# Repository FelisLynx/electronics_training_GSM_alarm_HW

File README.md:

# electronics_training_GSM_alarm_HW
Hardware for GSM alarm (electronics training group materials)

please check wiki for more information:
https://github.com/FelisLynx/electronics_training_GSM_alarm_HW/wiki

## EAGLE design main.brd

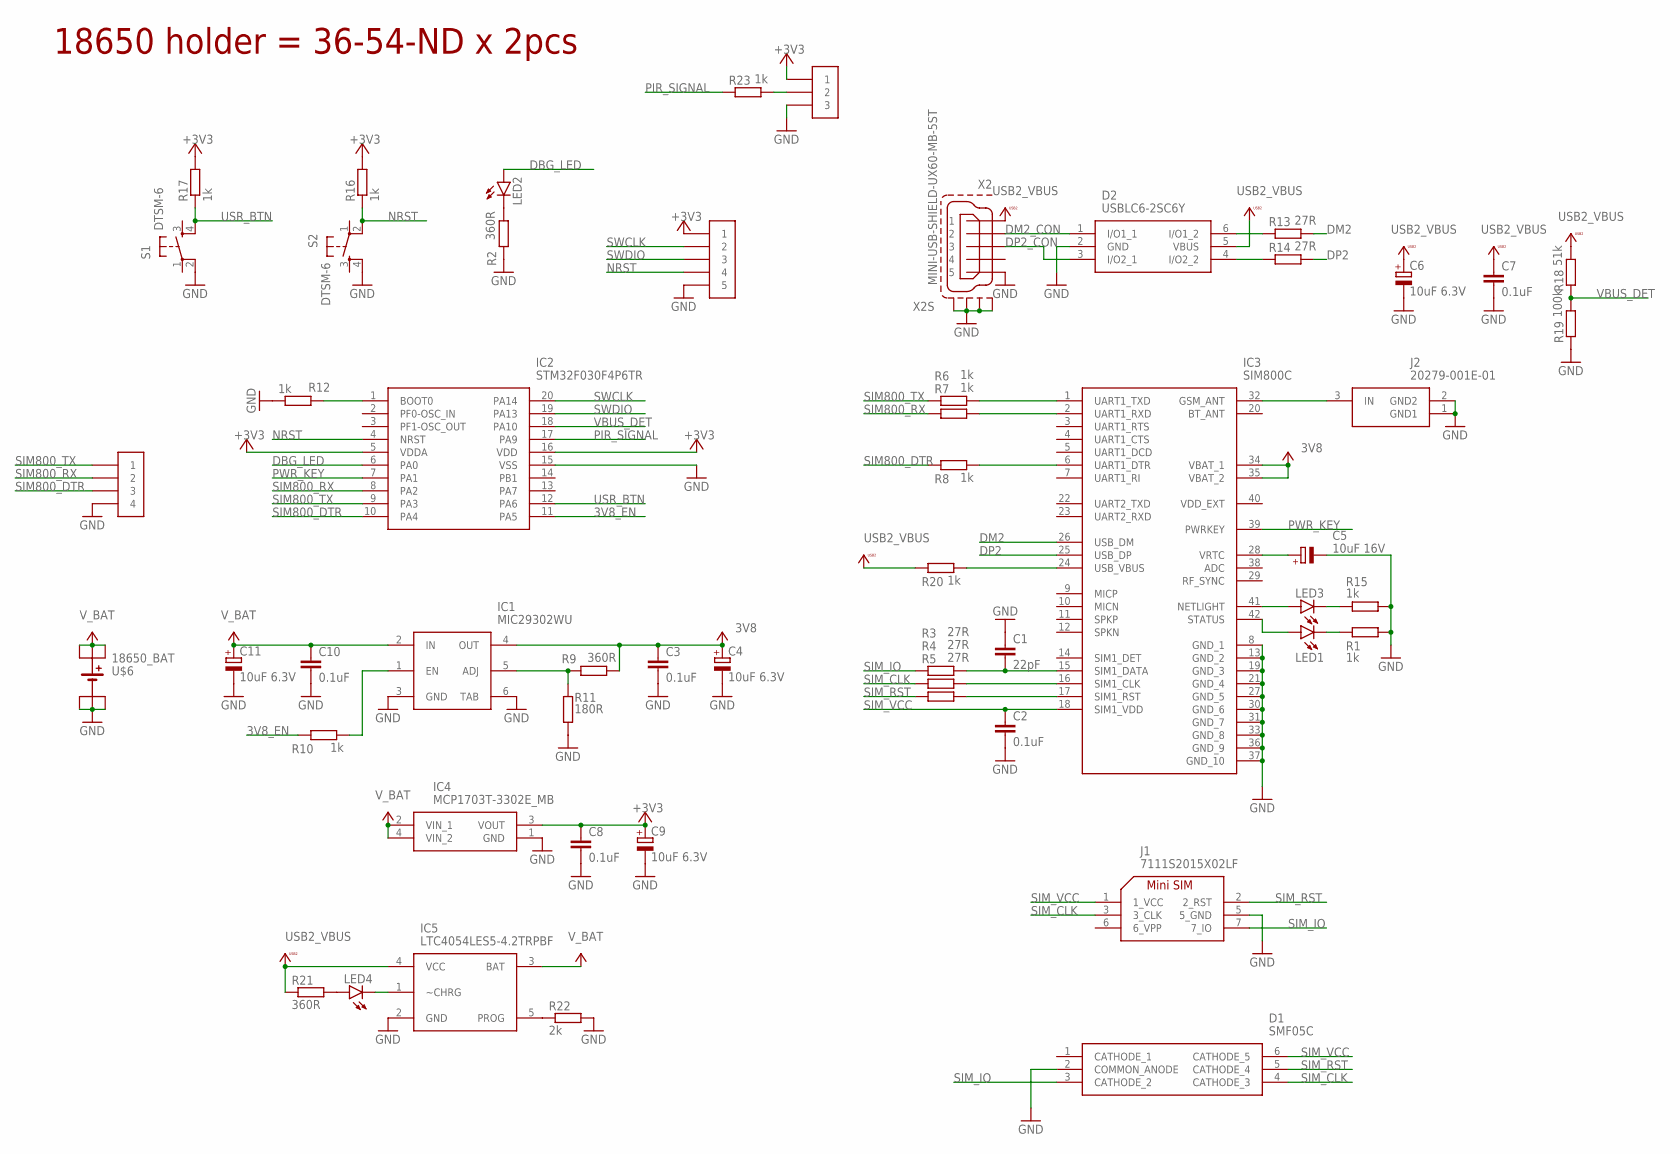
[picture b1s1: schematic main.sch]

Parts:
C1: 22pF; C0805
C2, C3, C7, C8, C10: 0.1uF; C0805
C4, C6, C9, C11: 10uF 6.3V; SMC_C
C5: 10uF 16V; SMC_C
D1: SMF05C; SOT65P210X110-6N
D2: USBLC6-2SC6Y; SOT95P280X145-6N
IC1: MIC29302WU
IC2: STM32F030F4P6TR; SOP65P640X120-20N
IC3: SIM800C
IC4: MCP1703T-3302E_MB; SOT-89(MB)
IC5: LTC4054LES5-4.2TRPBF; SOT95P280X100-5N
J1: 7111S2015X02LF
J2: 20279-001E-01
LED1, LED2, LED3, LED4: LEDCHIPLED_0805; CHIPLED_0805
R1, R6, R7, R8, R10, R12, R15, R16, R17, R20, R23: 1k; R0805
R2, R9, R21: 360R; R0805
R3, R4, R5, R13, R14: 27R; R0805
R11: 180R; R0805
R18: 51k; R0805
R19: 100k; R0805
R22: 2k; R0805
S1, S2: DTSM-6
U$5: 1R_4P
U$6: 18650_BAT
U$12: 1R_5P
U$15: 1R_3P
X2: MINI-USB-SHIELD-UX60-MB-5ST; UX60-MB-5ST

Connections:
3V8: C3.1, C4.+, IC1.4 (OUT), IC3.34 (VBAT_1), IC3.35 (VBAT_2), R9.2
3V8_EN: IC2.11 (PA5), R10.1
+3V3: C8.1, C9.+, IC2.5 (VDDA), IC2.16 (VDD), IC4.3 (VOUT), R16.2, R17.2, U$12.P$1 (1), U$15.P$1 (1)
DBG_LED: IC2.6 (PA0), LED2.A
DM2: IC3.26 (USB_DM), R13.2
DM2_CON: D2.1 (I/O1_1), X2.2
DP2: IC3.25 (USB_DP), R14.2
DP2_CON: D2.3 (I/O2_1), X2.3
GND: C1.1, C2.2, C3.2, C4.-, C5.-, C6.-, C7.2, C8.2, C9.-, C10.2, C11.-, D1.2 (COMMON_ANODE), D2.2 (GND), IC1.3 (GND), IC1.6 (TAB), IC2.15 (VSS), IC3.8 (GND_1), IC3.13 (GND_2), IC3.19 (GND_3), IC3.21 (GND_4), IC3.27 (GND_5), IC3.30 (GND_6), IC3.31 (GND_7), IC3.33 (GND_8), IC3.36 (GND_9), IC3.37 (GND_10), IC4.1 (GND), IC5.2 (GND), J1.5 (5_GND), J2.1 (GND1), J2.2 (GND2), R1.2, R2.1, R11.1, R12.2, R15.2, R19.1, R22.2, S1.2, S2.4, U$5.P$4 (4), U$6.4, U$6.5, U$6.6, U$12.P$5 (5), U$15.P$3 (3), X2.5, X2.M1 (S1), X2.M2 (S2), X2.M3 (S3), X2.M4 (S4)
unnamed: IC3.41 (NETLIGHT), LED3.A
unnamed: LED3.C, R15.1
unnamed: IC3.42 (STATUS), LED1.A
unnamed: LED1.C, R1.1
unnamed: IC3.32 (GSM_ANT), J2.3 (IN)
unnamed: C5.+, IC3.28 (VRTC)
unnamed: C1.2, IC3.15 (SIM1_DATA), R3.2
unnamed: IC3.16 (SIM1_CLK), R4.2
unnamed: IC3.17 (SIM1_RST), R5.2
unnamed: IC2.1 (BOOT0), R12.1
unnamed: IC3.1 (UART1_TXD), R6.2
unnamed: IC3.2 (UART1_RXD), R7.2
unnamed: IC3.6 (UART1_DTR), R8.2
unnamed: IC1.1 (EN), R10.2
unnamed: D2.6 (I/O1_2), R13.1
unnamed: IC1.5 (ADJ), R9.1, R11.2
unnamed: LED2.C, R2.2
unnamed: IC3.24 (USB_VBUS), R20.2
unnamed: D2.4 (I/O2_2), R14.1
unnamed: LED4.A, R21.2
unnamed: IC5.1 (~CHRG), LED4.C
unnamed: IC5.5 (PROG), R22.1
unnamed: R23.2, U$15.P$2 (2)
NRST: IC2.4 (NRST), R16.1, S2.2, U$12.P$4 (4)
PIR_SIGNAL: IC2.17 (PA9), R23.1
PWR_KEY: IC2.7 (PA1), IC3.39 (PWRKEY)
SIM800_DTR: IC2.10 (PA4), R8.1, U$5.P$3 (3)
SIM800_RX: IC2.8 (PA2), R7.1, U$5.P$2 (2)
SIM800_TX: IC2.9 (PA3), R6.1, U$5.P$1 (1)
SIM_CLK: D1.4 (CATHODE_3), J1.3 (3_CLK), R4.1
SIM_IO: D1.3 (CATHODE_2), J1.7 (7_IO), R3.1
SIM_RST: D1.5 (CATHODE_4), J1.2 (2_RST), R5.1
SIM_VCC: C2.1, D1.6 (CATHODE_5), IC3.18 (SIM1_VDD), J1.1 (1_VCC)
SWCLK: IC2.20 (PA14), U$12.P$2 (2)
SWDIO: IC2.19 (PA13), U$12.P$3 (3)
USB2_VBUS: C6.+, C7.1, D2.5 (VBUS), IC5.4 (VCC), R18.2, R20.1, R21.1, X2.1
USR_BTN: IC2.12 (PA6), R17.1, S1.4
VBUS_DET: IC2.18 (PA10), R18.1, R19.2
V_BAT: C10.1, C11.+, IC1.2 (IN), IC4.2 (VIN_1), IC4.4 (VIN_2), IC5.3 (BAT), U$6.1, U$6.2, U$6.3

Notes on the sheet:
18650 holder = 36-54-ND x 2pcs

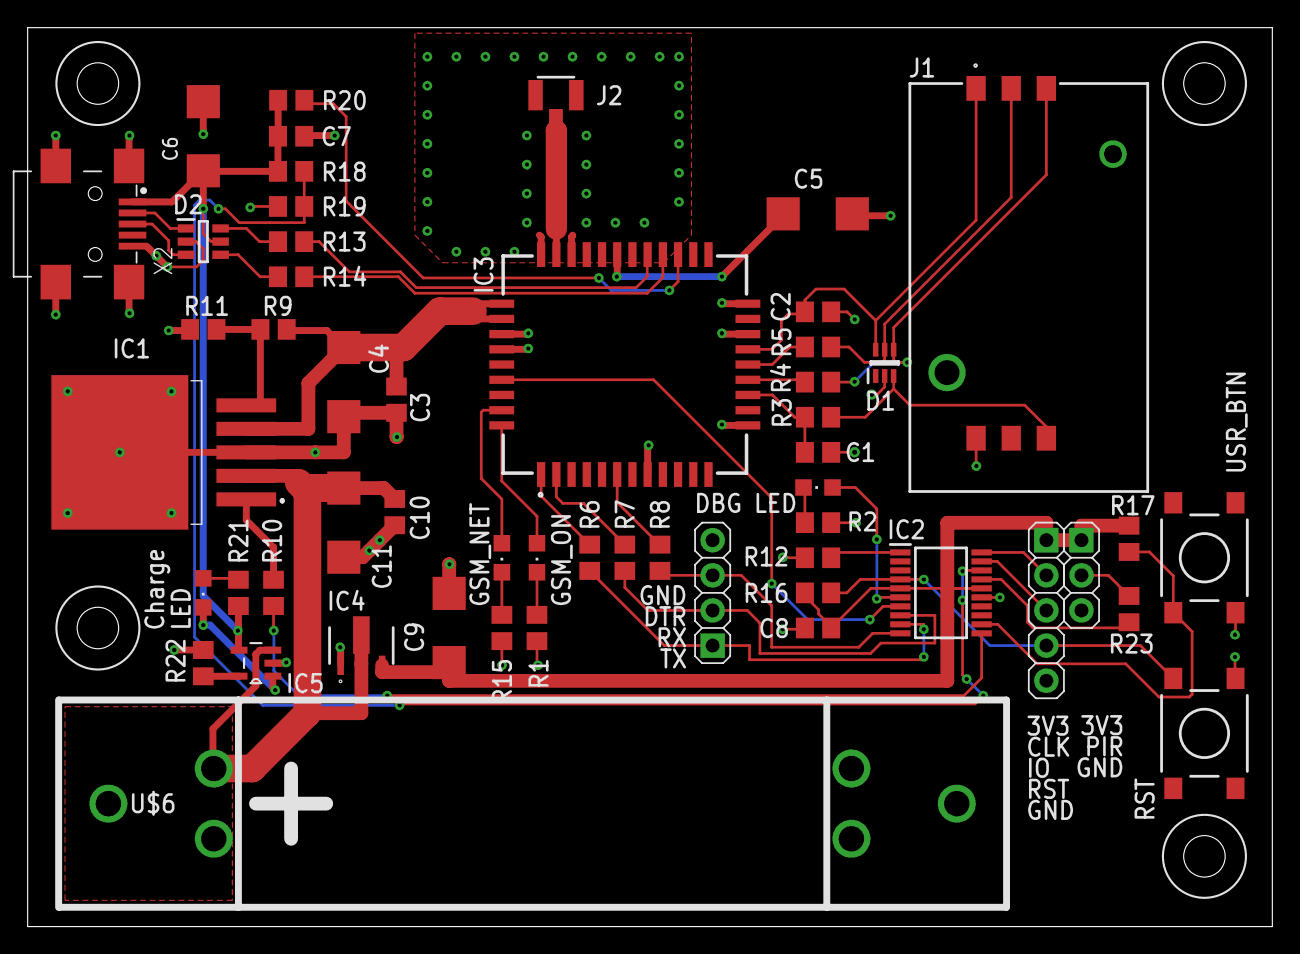
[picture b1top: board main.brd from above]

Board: 2 copper layers, 90.0 x 65.0 mm, 54 parts (0 on the bottom side), 48 nets.

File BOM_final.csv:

Qty,Value,Device,Package,Parts
1,,LEDCHIPLED_0805,SMD_0805,LED1
1,,LEDCHIPLED_0805,SMD_0805,LED2
2,,LEDCHIPLED_0805,SMD_0805,"LED3, LED4"
5,0.1uF,C-EUC0805,C0805,"C2, C3, C7, C8, C10"
5,10uF 6.3V,CPOL-EUSMCC,SMC_C,"C4, C5, C6, C9, C11"
1,180R,R-EU_R0805,R0805,R11
2,18650_BAT,18650_BAT,36-54-ND,U$6
1,1R_3P,1R_3P,1R_3P,U$15
11,1k,R-EU_R0805,R0805,"R1, R6, R7, R8, R10, R12, R15, R16, R17, R20, R23"
1,20279-001E-01,20279-001E-01,20279-001E-01,J2
1,22pF,C-EUC0805,C0805,C1
7,27R,R-EU_R0805,R0805,"R3, R4, R5, R13, R14"
1,100k,R-EU_R0806,R0806,R19
1,51k,R-EU_R0807,R0807,R18
1,2k,R-EU_R0805,R0805,R22
3,360R,R-EU_R0805,R0805,"R2, R9, R21"
1,7111S2015X02LF,7111S2015X02LF,7111S2015X02LF,J1
2,DTSM-6,DTSM-6,DTSM-6,"S1, S2"
1,LTC4054LES5-4.2TRPBF,LTC4054LES5-4.2TRPBF,SOT95P280X100-5N,IC5
1,MCP1703T-3302E_MB,MCP1703T-3302E_MB,SOT-89(MB),IC4
1,MIC29302WU,MIC29302WU,MIC29302WU,IC1
1,MINI-USB-CON,MINI-USB-CON,690-005-299-043,X2
1,SIM800C,SIM800C,SIM800C,IC3
1,SMF05C,SMF05C,SOT65P210X110-6N,D1
1,STM32F030F4P6TR,STM32F030F4P6TR,SOP65P640X120-20N,IC2
1,USBLC6-2SC6Y,USBLC6-2SC6Y,SOT95P280X145-6N,D2
2,18650_BAT_holder,18651_BAT_holder,18652_BAT_holder,"B1, B2"

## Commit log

2019-07-03 edited schematics, R18 and R19 values are now correct, edited USB connector
2019-07-03 add images for wiki
2019-07-03 image names edited
